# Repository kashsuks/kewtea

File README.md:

# kewtea
A 30% low profile ortholinear keyboard.

I've recently found that normal keyboards just have too much going on, so it's time to make things simple.

## Bill of Materials

| Name                                        | Quantity | Purpose                                 | Link                                                                  | Cost (CAD) | Cost (USD) |
|---------------------------------------------|----------|-----------------------------------------|-----------------------------------------------------------------------|------------|------------|
| Kailh Choc Low Profile Switches (set of 10) | 3        | Switches for the keys                   | https://typeractive.xyz/products/choc-switches?variant=51038935122151 | 24.00      | 17.40      |
| DO-35 Diodes (set of 50)                    | 1        | Diodes for the keys grid                | https://www.aliexpress.com/item/1005006711895793.html                 | 3.89       | 2.82       |
| 0.91 Inch 128x32 I2C OLED Display           | 1        | OLED display                            | https://www.aliexpress.com/item/1005008640132638.html                 | 3.27       | 2.37       |
| Pro Micro NRF52840                          | 1        | Cheaper alternative to nice!nano v2 mcu | https://www.aliexpress.com/item/1005009026511947.html                 | 5.67       | 4.11       |
| MBK Choc Keycaps (set of 10)                | 3        | Keycaps needed for the switches         | https://typeractive.xyz/products/mbk-keycaps                          | 15.00      | 10.87      |
| JLCPCB PCB Manufacturing                    | 1        | The actual pcb board                    | https://jlcpcb.com/                                                   | N/A        | 10.02      |
## Code

I used [kmk](https://github.com/KMKfw/kmk_firmware) along with the circuitpython Nice!nano `.UF2`. They can be used interchangeably with the Pro Micro NRF52840 since it's based off the nice!nano.

The code is yet to be thoroughly tested and will be done so after recieving the board :)

## Schematic

## PCB

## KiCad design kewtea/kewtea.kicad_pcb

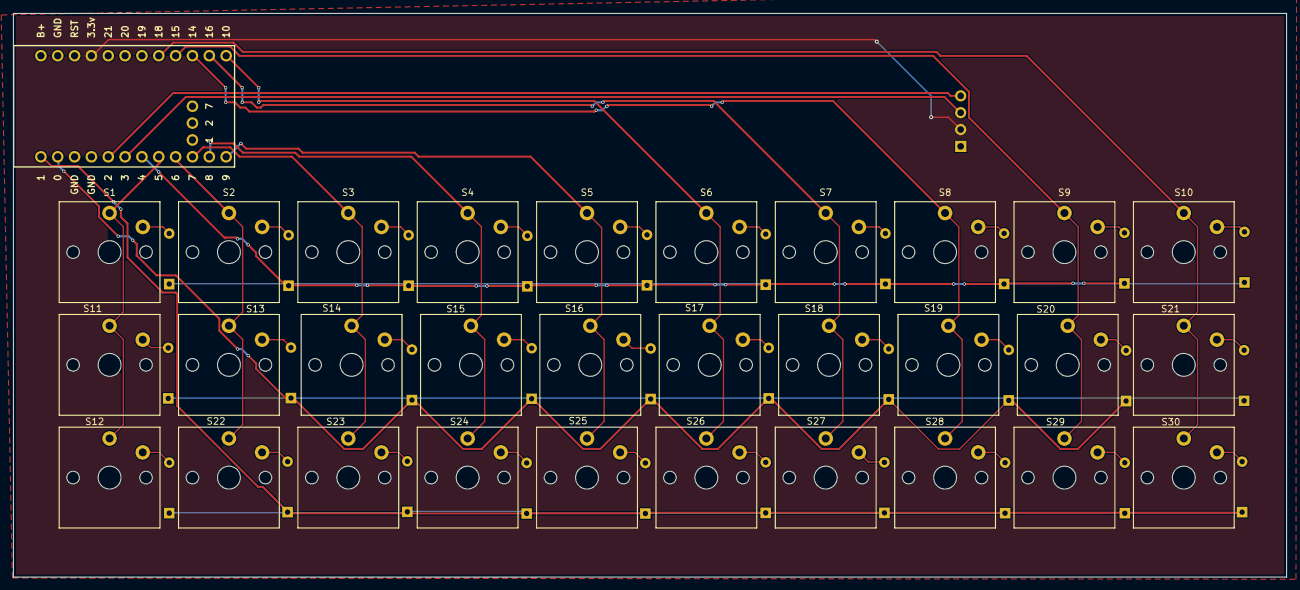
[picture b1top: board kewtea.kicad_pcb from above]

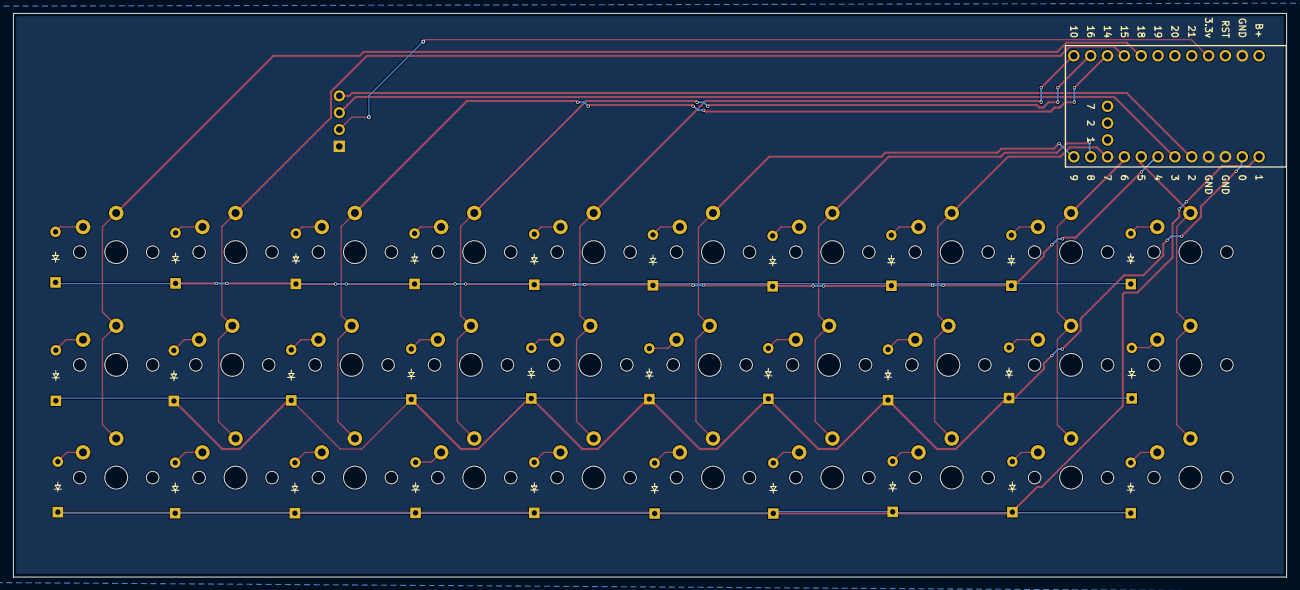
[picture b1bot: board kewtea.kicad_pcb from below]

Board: 2 copper layers, 192.0 x 85.0 mm, 62 parts (30 on the bottom side), 47 nets.

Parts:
D1, D2, D3, D4, D5, D6, D7, D8, D9, D10, D11, D12, D13, D14, D15, D16, D17, D18, D19, D20, D21, D22, D23, D24, D25, D26, D27, D28, D29, D30: Diode_DO-35
J1: OLED_128x32
S1, S2, S3, S4, S5, S6, S7, S8, S9, S10, S11, S12, S13, S14, S15, S16, S17, S18, S19, S20, S21, S22, S23, S24, S25, S26, S27, S28, S29, S30: Choc_V1
U1: Nice_Nano_V2

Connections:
COL0: S1.1, S11.1, S12.1, U1.8 (5)
COL1: S2.1, S13.1, S22.1, U1.9 (6)
COL2: S3.1, S14.1, S23.1, U1.10 (7)
COL3: S4.1, S15.1, S24.1, U1.11 (8)
COL4: S5.1, S16.1, S25.1, U1.12 (9)
COL5: S6.1, S17.1, S26.1, U1.13 (10)
COL6: S7.1, S18.1, S27.1, U1.14 (16)
COL7: S8.1, S19.1, S28.1, U1.15 (14)
COL8: S9.1, S20.1, S29.1, U1.16 (15)
COL9: S10.1, S21.1, S30.1, U1.17 (18)
GND: J1.1 (GND), U1.3 (GND), U1.4 (GND), U1.23 (GND)
unnamed: D1.2 (A), S1.2
unnamed: D2.2 (A), S2.2
unnamed: D3.2 (A), S3.2
unnamed: D4.2 (A), S4.2
unnamed: D5.2 (A), S5.2
unnamed: D6.2 (A), S6.2
unnamed: D7.2 (A), S7.2
unnamed: D8.2 (A), S8.2
unnamed: D9.2 (A), S9.2
unnamed: D10.2 (A), S10.2
unnamed: D11.2 (A), S11.2
unnamed: D12.2 (A), S12.2
unnamed: D13.2 (A), S13.2
unnamed: D14.2 (A), S14.2
unnamed: D15.2 (A), S15.2
unnamed: D16.2 (A), S16.2
unnamed: D17.2 (A), S17.2
unnamed: D18.2 (A), S18.2
unnamed: D19.2 (A), S19.2
unnamed: D20.2 (A), S20.2
unnamed: D21.2 (A), S21.2
unnamed: D22.2 (A), S22.2
unnamed: D23.2 (A), S23.2
unnamed: D24.2 (A), S24.2
unnamed: D25.2 (A), S25.2
unnamed: D26.2 (A), S26.2
unnamed: D27.2 (A), S27.2
unnamed: D28.2 (A), S28.2
unnamed: D29.2 (A), S29.2
unnamed: D30.2 (A), S30.2
ROW0: D1.1 (K), D2.1 (K), D3.1 (K), D4.1 (K), D5.1 (K), D6.1 (K), D7.1 (K), D8.1 (K), D9.1 (K), D10.1 (K), U1.7 (4)
ROW1: D11.1 (K), D13.1 (K), D14.1 (K), D15.1 (K), D16.1 (K), D17.1 (K), D18.1 (K), D19.1 (K), D20.1 (K), D21.1 (K), U1.2 (0)
ROW2: D12.1 (K), D22.1 (K), D23.1 (K), D24.1 (K), D25.1 (K), D26.1 (K), D27.1 (K), D28.1 (K), D29.1 (K), D30.1 (K), U1.1
SCL: J1.3 (SCL), U1.6 (3)
SDA: J1.4 (SDA), U1.5 (2)
VCC: J1.2 (VCC), U1.21 (3.3v)

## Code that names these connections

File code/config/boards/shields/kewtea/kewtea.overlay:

/*
 * kewtea.overlay
 *
 * Device-tree overlay for the kewtea 30% ortholinear keyboard shield.
 * Targets the nice_nano_v2 board (Pro Micro NRF52840 compatible).
 *
 * Matrix wiring  — all pins are on gpio0 (P0.xx):
 *   ROW0 = P0.04 | ROW1 = P0.00 | ROW2 = P0.01
 *   COL0..COL5  = P0.05–P0.10
 *   COL6..COL9  = P0.13–P0.16
 *
 * Note: P0.00 and P0.01 double as the 32.768 kHz LFXO pads on bare NRF52840
 * silicon. They are safe to use as GPIO here because BLE is disabled and no
 * external crystal is fitted on this board.
 *
 * OLED wiring (physical header pins, I2C0):
 *   SDA = P0.17 (header pin 5) | SCL = P0.20 (header pin 6)
 */

#include <dt-bindings/gpio/gpio.h>

/ {
    chosen {
        zmk,kscan   = &kscan0;
        zmk,display = &oled;
    };

    /**
     * @brief GPIO matrix keyboard scanner.
     *
     * Diode direction is row2col: row pins are driven HIGH one at a time,
     * column pins are sampled as inputs with pull-down resistors.
     * Flip to "col2row" here if keys register inverted after assembly.
     */
    kscan0: kscan {
        compatible = "zmk,kscan-gpio-matrix";
        diode-direction = "row2col";

        row-gpios
            = <&gpio0  4 GPIO_ACTIVE_HIGH>   /* ROW0 — Q..P */
            , <&gpio0  0 GPIO_ACTIVE_HIGH>   /* ROW1 — A..SEMI */
            , <&gpio0  1 GPIO_ACTIVE_HIGH>   /* ROW2 — Z..DOT */
            ;

        col-gpios
            = <&gpio0  5 (GPIO_ACTIVE_HIGH | GPIO_PULL_DOWN)>   /* COL0 */
            , <&gpio0  6 (GPIO_ACTIVE_HIGH | GPIO_PULL_DOWN)>   /* COL1 */
            , <&gpio0  7 (GPIO_ACTIVE_HIGH | GPIO_PULL_DOWN)>   /* COL2 */
            , <&gpio0  8 (GPIO_ACTIVE_HIGH | GPIO_PULL_DOWN)>   /* COL3 */
            , <&gpio0  9 (GPIO_ACTIVE_HIGH | GPIO_PULL_DOWN)>   /* COL4 */
            , <&gpio0 10 (GPIO_ACTIVE_HIGH | GPIO_PULL_DOWN)>   /* COL5 */
            , <&gpio0 13 (GPIO_ACTIVE_HIGH | GPIO_PULL_DOWN)>   /* COL6 */
            , <&gpio0 14 (GPIO_ACTIVE_HIGH | GPIO_PULL_DOWN)>   /* COL7 */
            , <&gpio0 15 (GPIO_ACTIVE_HIGH | GPIO_PULL_DOWN)>   /* COL8 */
            , <&gpio0 16 (GPIO_ACTIVE_HIGH | GPIO_PULL_DOWN)>   /* COL9 */
            ;
    };
};

/**
 * @brief I2C0 bus — hosts the SSD1306 OLED display.
 *
 * Pin assignment matches the nice_nano_v2 board definition:
 *   SDA = P0.17, SCL = P0.20.
 * The board DTS already declares pinctrl for i2c0; this node
 * enables the bus and attaches the display device.
 */
&i2c0 {
    status = "okay";

    /**
     * @brief Solomon SSD1306 — 128×32 monochrome OLED, I2C address 0x3C.
     *
     * Parameters are set for a standard 128×32 panel:
     *   - multiplex-ratio 31  (MUX = display height − 1)
     *   - com-sequential      (sequential COM pin configuration for 32-row panels)
     *   - segment-remap       (column address 127 maps to SEG0)
     *   - com-invdir          (scan from COM[N−1] to COM0 for correct orientation)
     */
    oled: ssd1306@3c {
        compatible = "solomon,ssd1306fb";
        reg = <0x3c>;
        width = <128>;
        height = <32>;
        segment-offset = <0>;
        page-offset = <0>;
        display-offset = <0>;
        multiplex-ratio = <31>;
        prechargep = <0x22>;
        segment-remap;
        com-invdir;
        com-sequential;
    };
};

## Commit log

2026-05-29 added layout
2026-05-29 add schematic with section outlines
2026-05-29 add pcb with 3d renders
2026-05-29 add generated drill files for pcb
2026-05-30 fix pcb zone fill issues
2026-05-30 fix unrouted vcc from nice!nano to 128x32 oled
2026-05-30 fix silkscreen and bad routing
2026-05-31 update dimensions for pcb
2026-05-31 create bom file
2026-05-31 add bom with parts for now (need to add m2 screws after modelling)
2026-05-31 feat: add ZMK shield for kewtea 30% ortholinear keyboard
    Implements the full ZMK user-config structure targeting nice_nano_v2:
    - 3×10 GPIO matrix (row2col, all pins on P0)
    - SSD1306 128×32 OLED over I2C0 (SDA=P0.17, SCL=P0.20)
    - Single-layer QWERTY keymap with space at ROW2/COL4
    - Custom status screen displaying uptime as HH:MM:SS
2026-05-31 kicad lock files
2026-05-31 ci: add ZMK GitHub Actions build workflow
2026-05-31 ci: replace reusable workflow with explicit build steps
    ZMK's reusable workflow expects build.yaml at the repo root, but
    this repo nests firmware under code/ alongside KiCad hardware files.
    The explicit workflow passes the correct config path to west and
    west build directly.
2026-05-31 fix: set west self path to code/config to anchor workspace at repo root
    west infers the workspace root by stripping the self.path suffix from
    the local manifest path. With self.path = config, west init -l code/config
    placed .west inside code/ instead of the repo root, causing west update
    to fail on the next CI step.
2026-05-31 fix: run west commands from code/ so workspace roots correctly
    west init -l always places .west in the parent of the given path,
    so west init -l code/config roots the workspace at code/, not the
    repo root. Use defaults.run.working-directory to run all west steps
    from code/ and revert the self.path change which had no effect on
    workspace root placement.
2026-05-31 fix: use nice_nano/v2 board name for Zephyr 4.x hardware model
    Zephyr 3.5+ replaced underscore-separated board variants with slash
    notation. nice_nano_v2 is now nice_nano/v2 in the new hardware model
    used by the zmk-build-arm:stable container (Zephyr 4.1.0).
2026-05-31 feat: replace ZMK with KMK firmware
    KMK runs on CircuitPython — no build system or compilation needed.
    Edit code/code.py directly on the CIRCUITPY USB drive.
    - 3x10 GPIO matrix via microcontroller.pin (P0.xx notation)
    - Single-layer QWERTY keymap with space at ROW2/COL4
    - SSD1306 128x32 OLED over I2C showing uptime as HH:MM:SS
    - CI reduced to a Python syntax check
2026-06-02 pcb with dimensions
2026-06-02 add the production cad files
2026-06-02 removed dimensions and made zone fill smaller
